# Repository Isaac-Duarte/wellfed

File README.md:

# Wellfed

Your pet's dinner shouldn't need the internet. Wellfed is open firmware for the **PETLIBRO Granary PLAF103** pet feeder. It runs the feeder on your own Wi-Fi, with no vendor cloud and no account. The Wellfed app and Home Assistant talk to it directly. The app runs on Android phones and on macOS, Linux and Windows computers.

> [!NOTE]
> Wellfed is in heavy development and isn't ready to look after a real pet yet. It feeds reliably on our test feeder, but it hasn't finished its long unattended run, and there's no release to install yet. We're an independent project, not affiliated with PETLIBRO.

## What works

- **Feeding.** Each feed stops on time, and a power cut never makes it feed twice. The feed button and the app both work.
- **Schedules.** Up to ten meal plans run on the feeder itself, with no phone or computer on.
- **Staying local.** The feeder joins your Wi-Fi, pairs over Bluetooth and only talks to the devices you pair with it.
- **Installing.** Wellfed installs over the air from the stock firmware. No screwdriver or soldering, and you can go back to stock the same way.
- **Updating.** If a new version fails to start, the feeder goes back to the one that worked.

The app and the Home Assistant integration are still in progress. The [roadmap](docs/roadmap.md) shows where each piece stands.

## Is it for you?

It's a good fit if you own a PLAF103, you're comfortable setting up a device on your home network, and you'd like to try a feeder that works without the cloud.

Wait a little longer if:

- a pet depends on the feeder for its meals;
- you want a finished phone app, or a release you can just install;
- you have a different feeder. Only the PLAF103 is supported for now;
- you can't risk the feeder. If an install goes badly wrong, getting it back means opening it up and wiring to its board.

## Learn more

| You want to… | Read |
| --- | --- |
| See what works and what's next | [Roadmap](docs/roadmap.md) |
| Learn how installing works | [Installation](docs/firmware/consumer-installation.md) |
| Understand how it fits together | [How Wellfed works](docs/firmware/product-architecture.md) |
| Find your way around every page | [Documentation index](docs/README.md) |
| Report a bug or a hardware finding | [Contributing](CONTRIBUTING.md) (we aren't taking pull requests yet) |

## Build it

You don't need a feeder to build and test Wellfed, and the checks never touch one. Install Rust through rustup, plus Make, CMake and a C compiler, then run:

```sh
cargo install cargo-nextest cargo-deny
cargo build --locked
make check
```

The [developer guide](docs/development/README.md) covers the rest: what each folder holds, which tool does what, and how to build a full firmware image.

## License

Wellfed is [MIT licensed](LICENSE). The test bench board in `src/hardware/bench/` is [CERN-OHL-P](src/hardware/bench/LICENSE), and dependencies keep their own licenses ([third-party provenance](THIRD_PARTY.md)). The repository contains no vendor firmware or device backups.

PETLIBRO and Granary are PETLIBRO's names, used here only to say which feeder Wellfed runs on.

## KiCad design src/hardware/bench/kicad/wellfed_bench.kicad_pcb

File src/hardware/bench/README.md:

# Wellfed Bench board

The Wellfed Bench is an RP2040 USB-C board for recovering and developing on PETLIBRO feeders. It replaces the FT232R UART adapter and SH-UR04A relay board of the [relay bench](../../../docs/devices/plaf103/bench.md). Over one USB cable it shows up as a feeder UART bridge plus an `AT+CHn` relay port, so the bench tools can drive it the way they drive the relay board. This page covers the hardware: what is on the board, the files here, and how to order it. The firmware has [its own page](../../firmware/bench/README.md).

> [!NOTE]
> Rev B is the only revision. One batch has been built. On November 2, 2026 one board passed the first four bring-up checks with nothing attached to its feeder side: it flashed, enumerated, switched feeder power (4.96 V out, no fault), the strap and both UART buffers, and moved to the aux input. The same day, with a stock feeder connected on macOS, it passed steps 5 to 7 apart from the D-cell refusal: the feeder drew 89 to 131 mA with ALIVE 1, `wellfed-bench serve` drove `status`, `on`, `off` and `loader` through it, RECOVER's long press reached the ROM loader, and `wellfed-flash` read the feeder's whole 8 MiB flash through its bridge. The current has not been checked against a meter yet.

## What it does

- **Feeder power.** A switched 5 V USB-A output (AP2171W, about 1.1 A limit) with an overcurrent flag, voltage and current sensing (INA181 on 50 mΩ).
- **Loader strap.** Holds feeder TX to GND through 4.7 kΩ, the ROM loader entry.
- **UART isolation.** A 74LVC2G125 buffer per direction, so the bridge cannot back-power a feeder that is off.
- **Aux power.** A second USB-C input, routed to the feeder by a TPS2116 when the host port cannot supply enough.
- **Feeder-alive sense.** Reads the feeder's TX level, so the board can tell that the D-cells still power a feeder whose 5 V is cut.
- **RECOVER button.** Power-cycles the feeder into its ROM loader without a host.
- **Room to grow.** 16 MB of flash (the firmware uses the first 2 MB), a 2×8 expansion header and an SWD header.

The relay channels, LEDs, buttons and pin map are listed in the [firmware page](../../firmware/bench/README.md#relay-port). The connectors, the FEEDER UART pinout and how to wire a feeder are on the [bench hardware](../../../docs/development/bench-hardware.md) page. The header's labels name the feeder's pins, so a feeder is wired label to label, TX to TX.

## Files

| Path | Contents |
| --- | --- |
| `kicad/` | The KiCad 10 project `wellfed_bench`: schematic, board and the `wellfed` symbol library |
| `fab/` | JLCPCB assembly files: the BOM and the placement file. Export the gerbers from `kicad/` (below) |
| `enclosure/` | The OpenSCAD two-part enclosure and its button caps |

## Order from JLCPCB

1. Export the gerbers (F/B copper, paste, silkscreen and mask, Edge.Cuts) and the PTH and NPTH Excellon drill files from `kicad/wellfed_bench.kicad_pcb`, zip them, and upload the zip.
2. Turn on assembly, then upload `fab/wellfed_bench-BOM.csv` and `fab/wellfed_bench-CPL-jlcrot.csv`.
3. Set "Confirm Parts Placement" to Yes, and check every pin 1 and LED polarity in their review.

The `-jlcrot` placement file has JLCPCB's rotations and the J4 position corrected by hand. Regenerating it from KiCad loses those corrections, so edit it rather than replace it when parts move.

## Print the enclosure

The enclosure is two printed parts plus three button caps, held by four M3×12 screws into nuts pressed into the base. The assembly notes are at the top of the `.scad` file. Render each part to STL:

```sh
cd src/hardware/bench/enclosure
openscad -D 'part="base"' -o base.stl wellfed_bench_enclosure.scad
openscad -D 'part="lid"' -o lid.stl wellfed_bench_enclosure.scad
openscad -D 'part="button"' -o button.stl wellfed_bench_enclosure.scad
```

The STLs are not tracked. The base is sized for SLA resin, which cracks if screws self-tap into it.

## Edit the design

Open `kicad/wellfed_bench.kicad_pro` in KiCad 10. The board's logo is the one-color Wellfed lockup from [assets/brand](../../../assets/brand/README.md), flattened into hole-free polygons and mirrored on the back silkscreen.

After a board change, regenerate the gerbers and check the BOM and placement file against it before ordering.

## License

The board design, fab outputs and enclosure in this folder are licensed under the [CERN Open Hardware Licence v2, Permissive](LICENSE) (CERN-OHL-P). The firmware is MIT, like the rest of the repository.

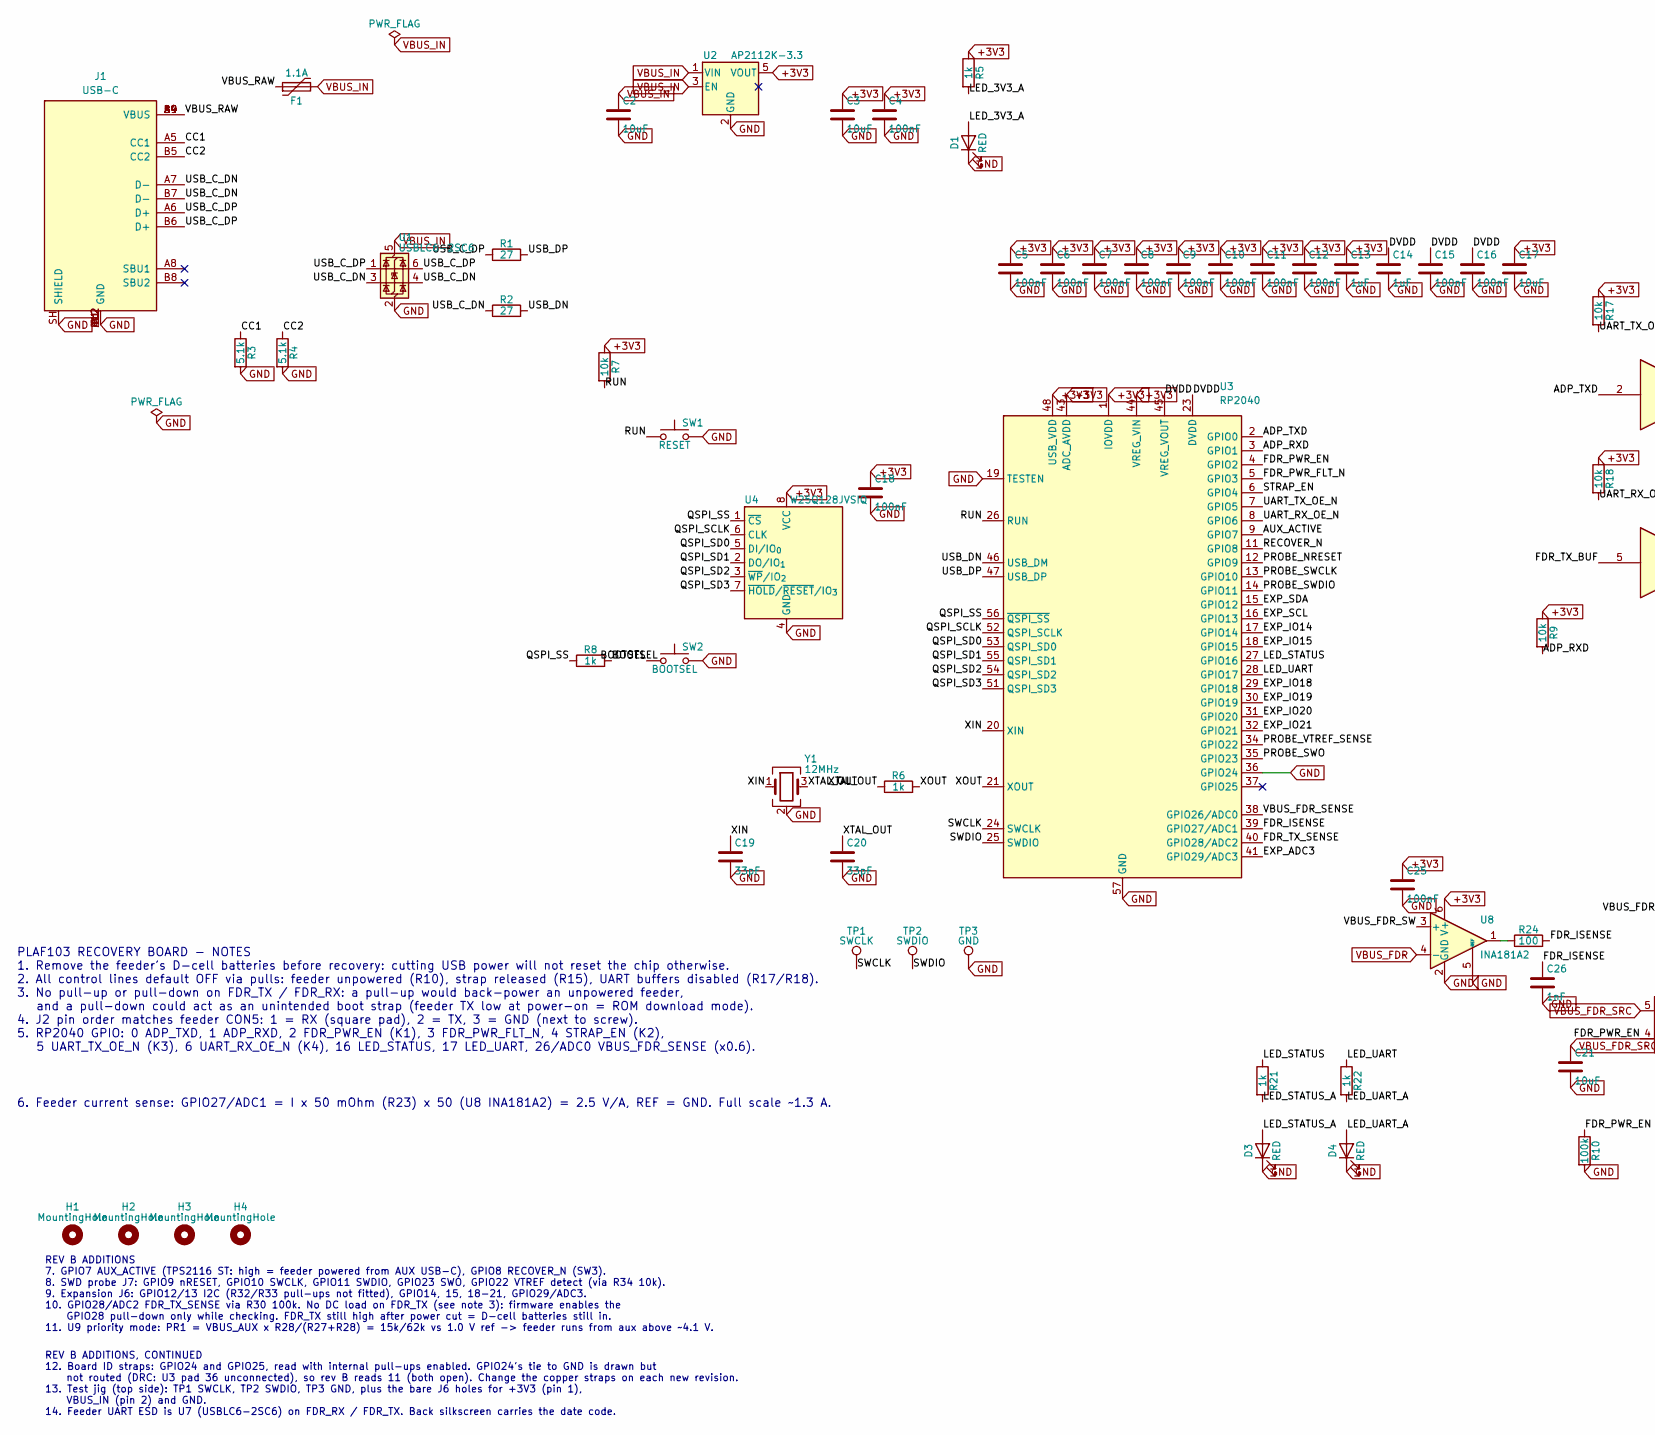
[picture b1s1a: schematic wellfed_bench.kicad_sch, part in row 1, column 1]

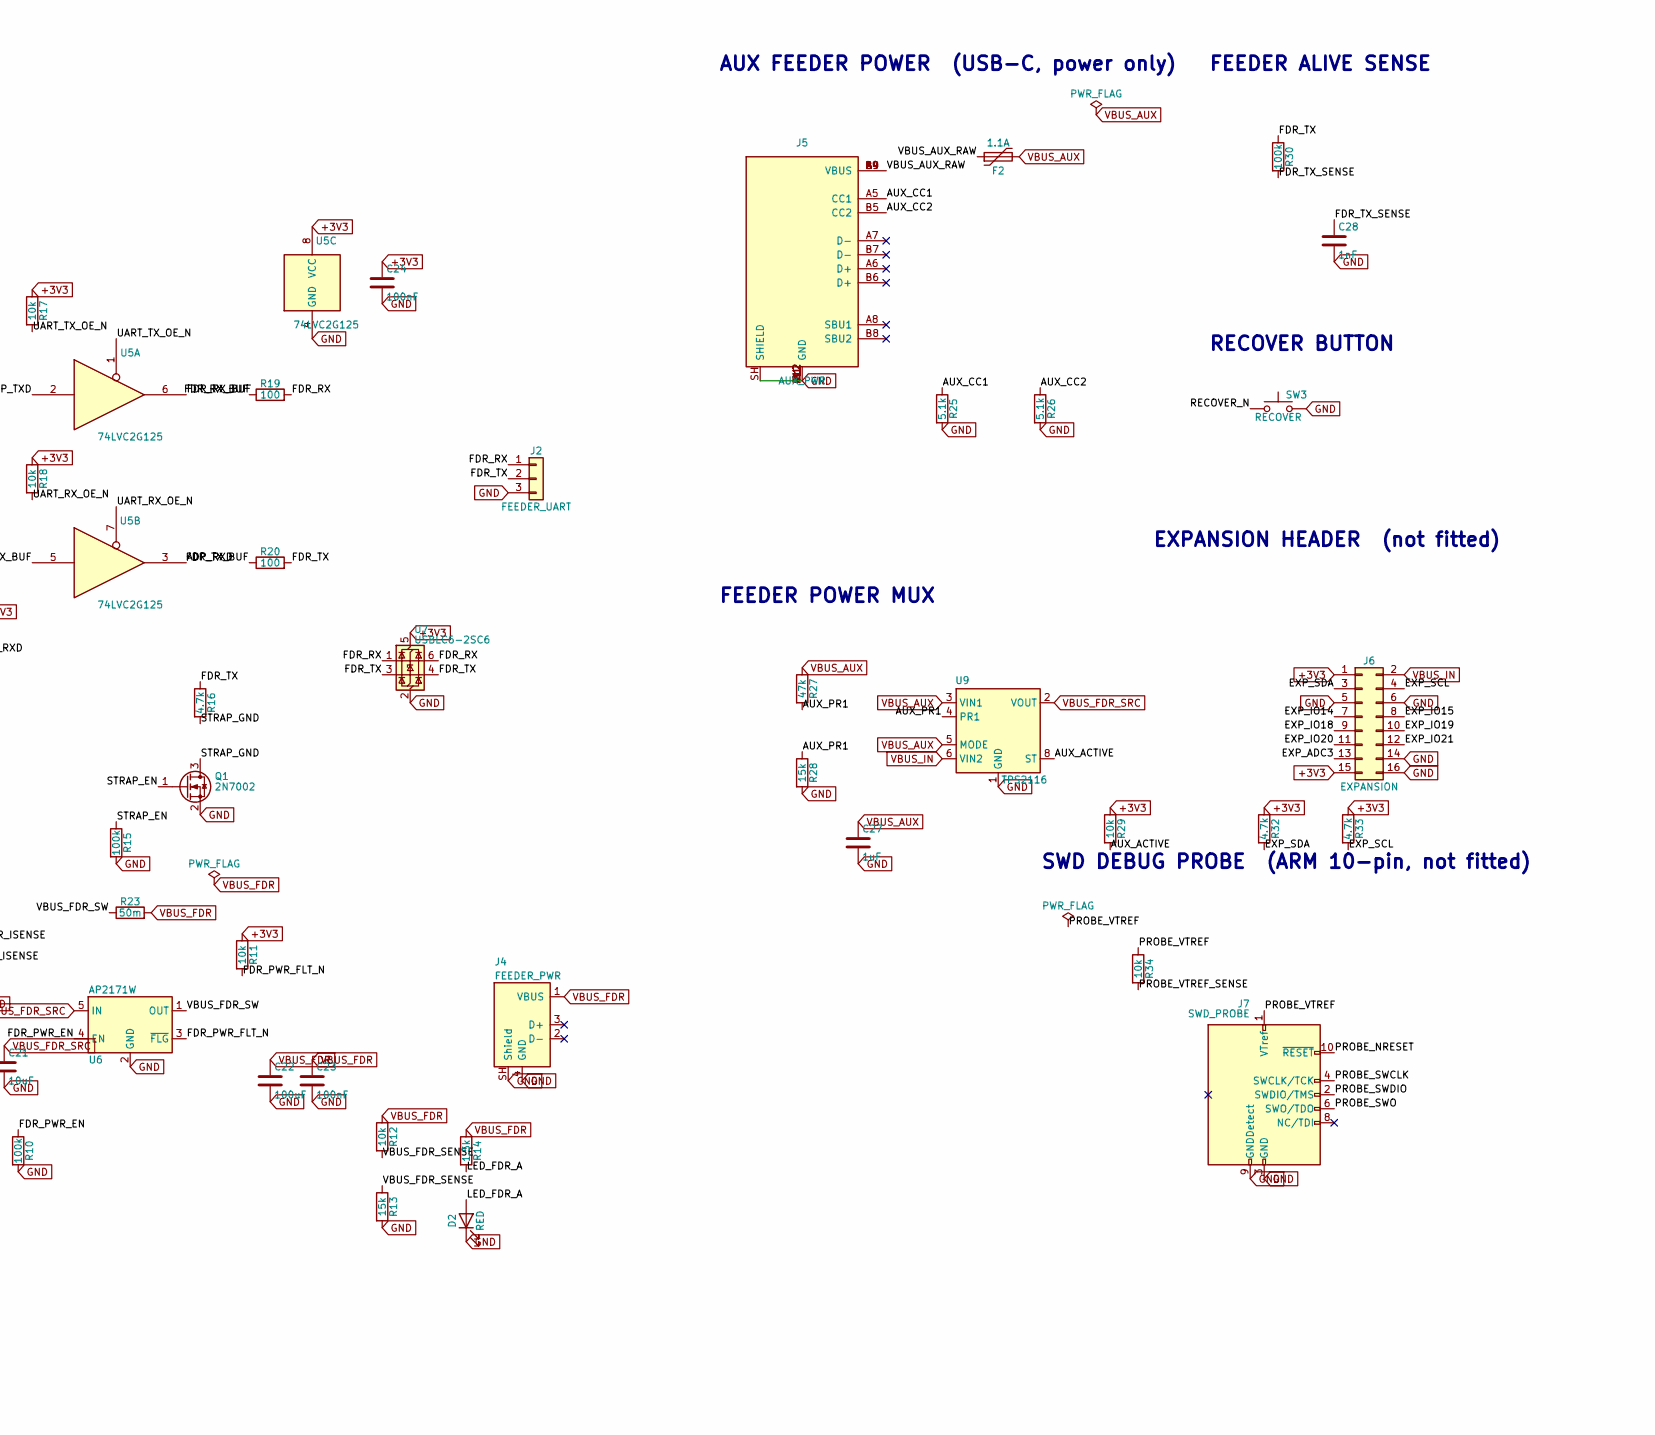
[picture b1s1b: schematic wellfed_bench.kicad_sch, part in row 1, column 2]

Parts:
C2, C3, C17: 10uF; C_0603_1608Metric; LCSC C19702
C4, C5, C6, C7, C8, C9, C10, C11, C12, C15, C16, C18, C23, C24, C25: 100nF; C_0402_1005Metric; LCSC C1525
C13, C14, C27: 1uF; C_0402_1005Metric; LCSC C52923
C19, C20: 33pF; C_0402_1005Metric; LCSC C1562
C21: 10uF; C_0402_1005Metric; LCSC C15525
C22: 100uF; C_1206_3216Metric; LCSC C15008
C26, C28: 1nF; C_0402_1005Metric; LCSC C1523
D1, D2, D3, D4: RED; LED_0603_1608Metric; LCSC C2286
F1, F2: 1.1A; Fuse_1206_3216Metric; MPN 1206L110THYR; LCSC C126818
H1, H2, H3, H4: MountingHole; MountingHole_3.2mm_M3
J1: USB-C; USB_C_Receptacle_HRO_TYPE-C-31-M-12; MPN TYPE-C-31-M-12; LCSC C165948
J2: FEEDER_UART; JST_PH_B3B-PH-K_1x03_P2.00mm_Vertical; MPN B3B-PH-K-S; LCSC C131339
J4: FEEDER_PWR; USB_A_Molex_67643_Horizontal; MPN 676430910; LCSC C2798029
J5: AUX_PWR; USB_C_Receptacle_HRO_TYPE-C-31-M-12; MPN TYPE-C-31-M-12; LCSC C165948
J6: EXPANSION; PinHeader_2x08_P2.54mm_Vertical
J7: SWD_PROBE; PinHeader_2x05_P1.27mm_Vertical
Q1: 2N7002; SOT-23; LCSC C8545
R1, R2: 27; R_0402_1005Metric; LCSC C25100
R3, R4, R25, R26: 5.1k; R_0402_1005Metric; LCSC C25905
R5, R6, R8, R21, R22: 1k; R_0402_1005Metric; LCSC C11702
R7, R9, R11, R12, R17, R18, R29, R34: 10k; R_0402_1005Metric; LCSC C25744
R10, R15, R30: 100k; R_0402_1005Metric; LCSC C25741
R13, R28: 15k; R_0402_1005Metric; LCSC C25756
R14: 1.5k; R_0402_1005Metric; LCSC C25867
R16, R32, R33: 4.7k; R_0402_1005Metric; LCSC C25900
R19, R20, R24: 100; R_0402_1005Metric; LCSC C25076
R23: 50m; R_1206_3216Metric; MPN FRM121WFR050TM; LCSC C7467249
R27: 47k; R_0402_1005Metric; LCSC C25792
SW1: RESET; SW_Push_1P1T_XKB_TS-1187A; LCSC C318884
SW2: BOOTSEL; SW_Push_1P1T_XKB_TS-1187A; LCSC C318884
SW3: RECOVER; SW_Push_1P1T_XKB_TS-1187A; LCSC C318884
TP1: SWCLK; TestPoint_Pad_D1.5mm
TP2: SWDIO; TestPoint_Pad_D1.5mm
TP3: GND; TestPoint_Pad_D1.5mm
U1, U7: USBLC6-2SC6; SOT-23-6; LCSC C21713975
U2: AP2112K-3.3; SOT-23-5; LCSC C22365427
U3: RP2040; QFN-56-1EP_7x7mm_P0.4mm_EP3.2x3.2mm; LCSC C2040
U4: W25Q128JVSIQ; SOIC-8_5.3x5.3mm_P1.27mm; MPN W25Q128JVSIQ; LCSC C97521
U5: 74LVC2G125; VSSOP-8_2.3x2mm_P0.5mm; MPN SN74LVC2G125DCUR; LCSC C21404
U6: AP2171W; SOT-23-5; MPN AP2171WG-7; LCSC C110466
U8: INA181A2; SOT-23-6; MPN INA181A2IDBVR; LCSC C2058784
U9: TPS2116; SOT-583-8; MPN TPS2116DRLR; LCSC C3235557
Y1: 12MHz; Crystal_SMD_3225-4Pin_3.2x2.5mm; MPN X322512MSB4SI; LCSC C9002

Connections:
+3V3: C3.1, C4.1, C5.1, C6.1, C7.1, C8.1, C9.1, C10.1, C11.1, C12.1, C13.1, C17.1, C18.1, C24.1, C25.1, J6.1, J6.15, R5.1, R7.1, R9.1, R11.1, R17.1, R18.1, R29.1, R32.1, R33.1, U2.5 (VOUT), U3.1 (IOVDD), U3.10 (IOVDD), U3.22 (IOVDD), U3.33 (IOVDD), U3.42 (IOVDD), U3.43 (ADC_AVDD), U3.44 (VREG_VIN), U3.48 (USB_VDD), U3.49 (IOVDD), U4.8 (VCC), U5.8 (VCC), U7.5 (VBUS), U8.6 (V+)
/ADP_RXD: R9.2, U3.3 (GPIO1), U5.3
/ADP_TXD: U3.2 (GPIO0), U5.2
/AUX_ACTIVE: R29.2, U3.9 (GPIO7), U9.8 (ST)
/AUX_CC1: J5.A5 (CC1), R25.1
/AUX_CC2: J5.B5 (CC2), R26.1
/AUX_PR1: R27.2, R28.1, U9.4 (PR1)
/BOOTSEL: R8.2, SW2.1
/CC1: J1.A5 (CC1), R3.1
/CC2: J1.B5 (CC2), R4.1
/DVDD: C14.1, C15.1, C16.1, U3.23 (DVDD), U3.45 (VREG_VOUT), U3.50 (DVDD)
/EXP_ADC3: J6.13, U3.41 (GPIO29/ADC3)
/EXP_IO14: J6.7, U3.17 (GPIO14)
/EXP_IO15: J6.8, U3.18 (GPIO15)
/EXP_IO18: J6.9, U3.29 (GPIO18)
/EXP_IO19: J6.10, U3.30 (GPIO19)
/EXP_IO20: J6.11, U3.31 (GPIO20)
/EXP_IO21: J6.12, U3.32 (GPIO21)
/EXP_SCL: J6.4, R33.2, U3.16 (GPIO13)
/EXP_SDA: J6.3, R32.2, U3.15 (GPIO12)
/FDR_ISENSE: C26.1, R24.2, U3.39 (GPIO27/ADC1)
/FDR_PWR_EN: R10.1, U3.4 (GPIO2), U6.4 (EN)
/FDR_PWR_FLT_N: R11.2, U3.5 (GPIO3), U6.3 (~FLG)
/FDR_RX: J2.1, R19.2, U7.1 (I/O1), U7.6 (I/O1)
/FDR_RX_BUF: R19.1, U5.6
/FDR_TX: J2.2, R16.1, R20.2, R30.1, U7.3 (I/O2), U7.4 (I/O2)
/FDR_TX_BUF: R20.1, U5.5
/FDR_TX_SENSE: C28.1, R30.2, U3.40 (GPIO28/ADC2)
/LED_3V3_A: D1.2 (A), R5.2
/LED_FDR_A: D2.2 (A), R14.2
/LED_STATUS: R21.1, U3.27 (GPIO16)
/LED_STATUS_A: D3.2 (A), R21.2
/LED_UART: R22.1, U3.28 (GPIO17)
/LED_UART_A: D4.2 (A), R22.2
/PROBE_NRESET: J7.10 (~RESET), U3.12 (GPIO9)
/PROBE_SWCLK: J7.4 (SWCLK/TCK), U3.13 (GPIO10)
/PROBE_SWDIO: J7.2 (SWDIO/TMS), U3.14 (GPIO11)
/PROBE_SWO: J7.6 (SWO/TDO), U3.35 (GPIO23)
/PROBE_VTREF: J7.1 (VTref), R34.1
/PROBE_VTREF_SENSE: R34.2, U3.34 (GPIO22)
/QSPI_SCLK: U3.52 (QSPI_SCLK), U4.6 (CLK)
/QSPI_SD0: U3.53 (QSPI_SD0), U4.5 (DI/IO_{0})
/QSPI_SD1: U3.55 (QSPI_SD1), U4.2 (DO/IO_{1})
/QSPI_SD2: U3.54 (QSPI_SD2), U4.3 (~WP/IO_{2})
/QSPI_SD3: U3.51 (QSPI_SD3), U4.7 (~HOLD/~RESET/IO_{3})
/QSPI_SS: R8.1, U3.56 (~QSPI_SS), U4.1 (~CS)
/RECOVER_N: SW3.1, U3.11 (GPIO8)
/RUN: R7.2, SW1.1, U3.26 (RUN)
/STRAP_EN: Q1.1 (G), R15.1, U3.6 (GPIO4)
/STRAP_GND: Q1.3 (D), R16.2
/SWCLK: TP1.1 (1_1), U3.24 (SWCLK)
/SWDIO: TP2.1 (1_1), U3.25 (SWDIO)
/UART_RX_OE_N: R18.2, U3.8 (GPIO6), U5.7
/UART_TX_OE_N: R17.2, U3.7 (GPIO5), U5.1
/USB_C_DN: J1.A7 (D-), J1.B7 (D-), R2.1, U1.3 (I/O2), U1.4 (I/O2)
/USB_C_DP: J1.A6 (D+), J1.B6 (D+), R1.1, U1.1 (I/O1), U1.6 (I/O1)
/USB_DN: R2.2, U3.46 (USB_DM)
/USB_DP: R1.2, U3.47 (USB_DP)
/VBUS_AUX_RAW: F2.1, J5.A4 (VBUS), J5.A9 (VBUS), J5.B4 (VBUS), J5.B9 (VBUS)
/VBUS_FDR_SENSE: R12.2, R13.1, U3.38 (GPIO26/ADC0)
/VBUS_FDR_SW: R23.1, U6.1 (OUT), U8.3 (+)
/VBUS_RAW: F1.1, J1.A4 (VBUS), J1.A9 (VBUS), J1.B4 (VBUS), J1.B9 (VBUS)
/XIN: C19.1, U3.20 (XIN), Y1.1
/XOUT: R6.2, U3.21 (XOUT)
/XTAL_OUT: C20.1, R6.1, Y1.3
GND: C2.2, C3.2, C4.2, C5.2, C6.2, C7.2, C8.2, C9.2, C10.2, C11.2, C12.2, C13.2, C14.2, C15.2, C16.2, C17.2, C18.2, C19.2, C20.2, C21.2, C22.2, C23.2, C24.2, C25.2, C26.2, C27.2, C28.2, D1.1 (K), D2.1 (K), D3.1 (K), D4.1 (K), J1.A1 (GND), J1.A12 (GND), J1.B1 (GND), J1.B12 (GND), J1.SH (SHIELD), J2.3, J4.4 (GND), J4.SH (Shield), J5.A1 (GND), J5.A12 (GND), J5.B1 (GND), J5.B12 (GND), J5.SH (SHIELD), J6.5, J6.6, J6.14, J6.16, J7.3 (GND), J7.5 (GND), J7.9 (GNDDetect), Q1.2 (S), R3.2, R4.2, R10.2, R13.2, R15.2, R25.2, R26.2, R28.2, SW1.2, SW2.2, SW3.2, TP3.1 (1_1), U1.2 (GND), U2.2 (GND), U3.19 (TESTEN), U3.36 (GPIO24), U3.57 (GND), U4.4 (GND), U5.4 (GND), U6.2 (GND), U7.2 (GND), U8.2 (GND), U8.5 (REF), U9.1 (GND), Y1.2 (G), Y1.4 (G)
unnamed: R24.1, U8.1
VBUS_AUX: C27.1, F2.2, R27.1, U9.3 (VIN1), U9.5 (MODE)
VBUS_FDR: C22.1, C23.1, J4.1 (VBUS), R12.1, R14.1, R23.2, U8.4 (-)
VBUS_FDR_SRC: C21.1, U6.5 (IN), U9.2 (VOUT), U9.7 (VOUT)
VBUS_IN: C2.1, F1.2, J6.2, U1.5 (VBUS), U2.1 (VIN), U2.3 (EN), U9.6 (VIN2)

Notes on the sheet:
EXPANSION HEADER (not fitted)
6. Feeder current sense: GPIO27/ADC1 = I x 50 mOhm (R23) x 50 (U8 INA181A2) = 2.5 V/A, REF = GND. Full scale ~1.3 A.
FEEDER POWER MUX
REV B ADDITIONS 7. GPIO7 AUX_ACTIVE (TPS2116 ST: high = feeder powered from AUX USB-C), GPIO8 RECOVER_N (SW3). 8. SWD probe J7: GPIO9 nRESET, GPIO10 SWCLK, GPIO11 SWDIO, GPIO23 SWO, GPIO22 VTREF detect (via R34 10k). 9. Expansion J6: GPIO12/13 I2C (R32/R33 pull-ups not fitted), GPIO14, 15, 18-21, G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
FEEDER ALIVE SENSE
AUX FEEDER POWER (USB-C, power only)
PLAF103 RECOVERY BOARD - NOTES 1. Remove the feeder's D-cell batteries before recovery: cutting USB power will not reset the chip otherwise. 2. All control lines default OFF via pulls: feeder unpowered (R10), strap released (R15), UART buffers disabled (R17/R18). 3. No pull-up or pull-down on FDR_T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
SWD DEBUG PROBE (ARM 10-pin, not fitted)
REV B ADDITIONS, CONTINUED 12. Board ID straps: GPIO24 and GPIO25, read with internal pull-ups enabled. GPIO24's tie to GND is drawn but not routed (DRC: U3 pad 36 unconnected), so rev B reads 11 (both open). Change the copper straps on each new revision. 13. Test jig (top side): TP1 SWCLK, TP2 SWD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
RECOVER BUTTON

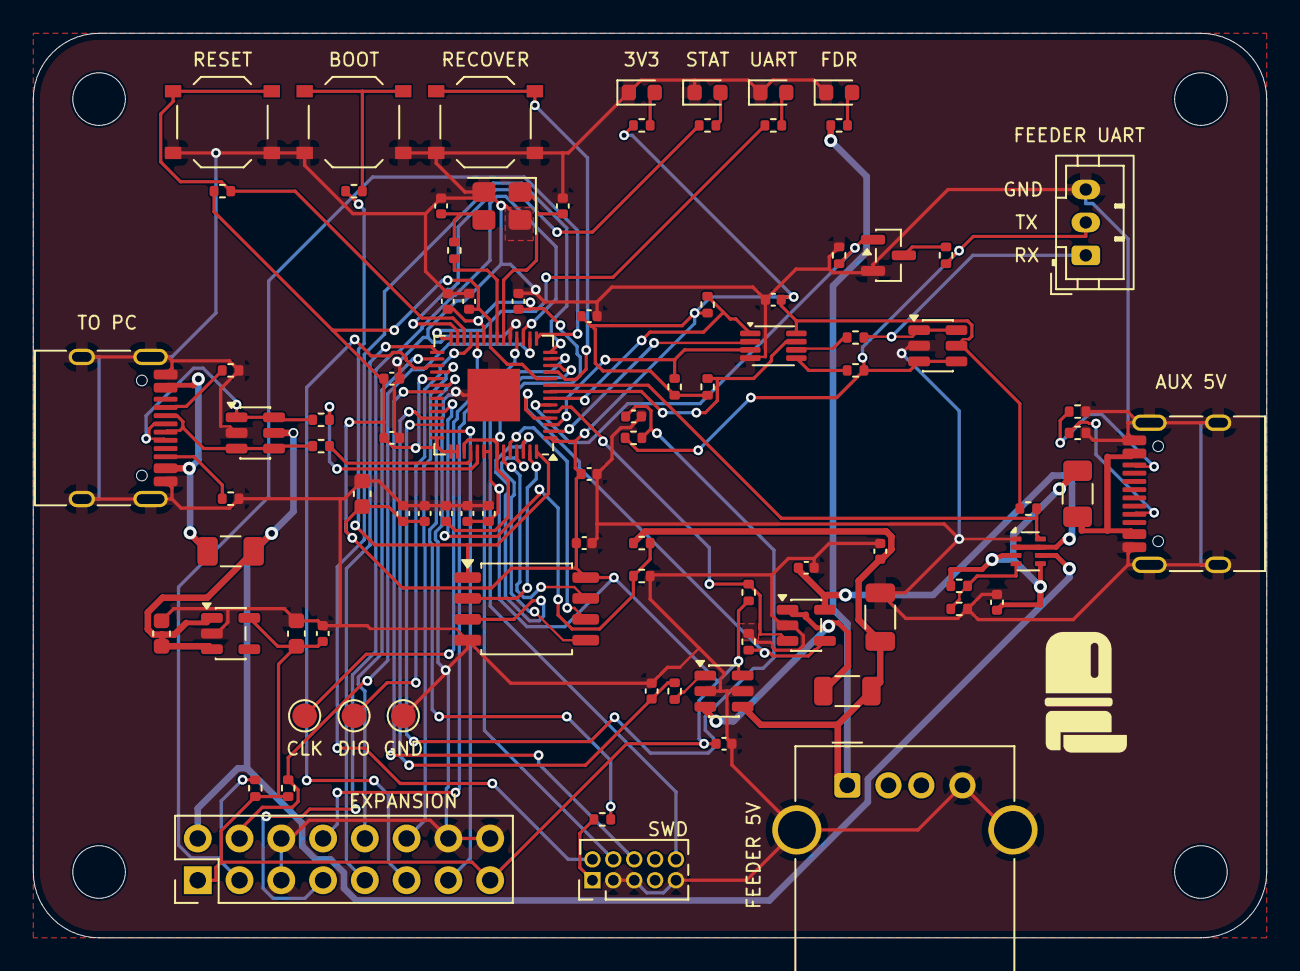
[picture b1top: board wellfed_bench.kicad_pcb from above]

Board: 2 copper layers, 75.0 x 55.0 mm, 93 parts (0 on the bottom side), 71 nets.
